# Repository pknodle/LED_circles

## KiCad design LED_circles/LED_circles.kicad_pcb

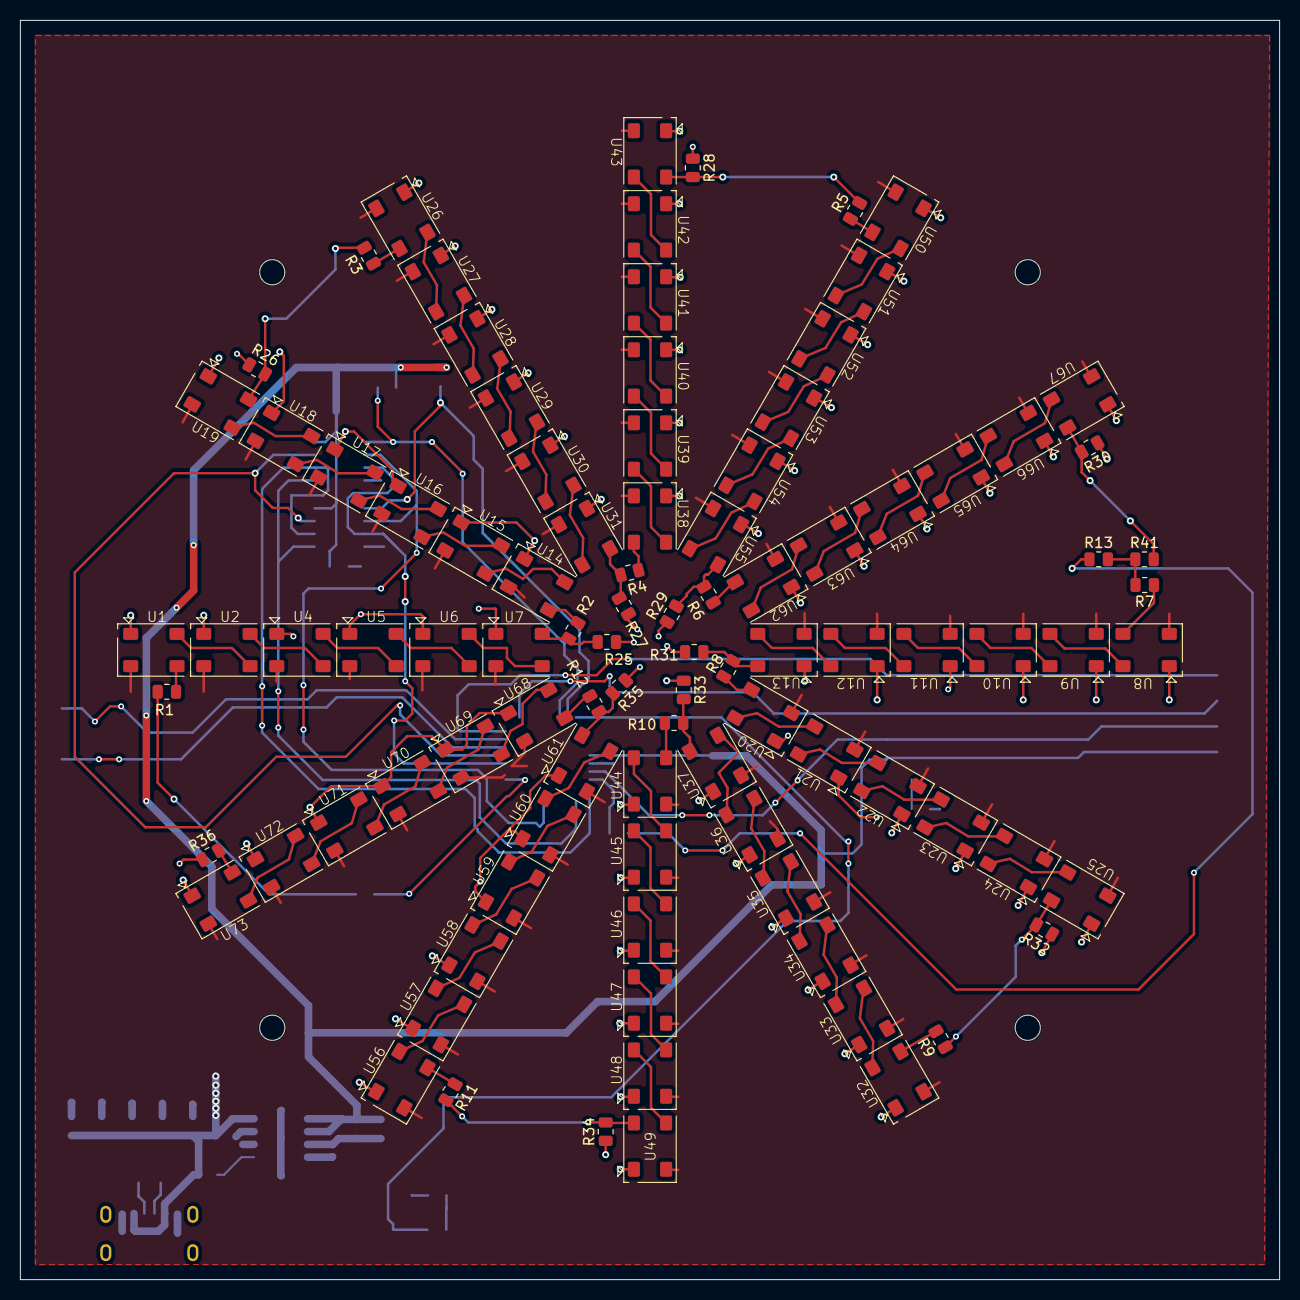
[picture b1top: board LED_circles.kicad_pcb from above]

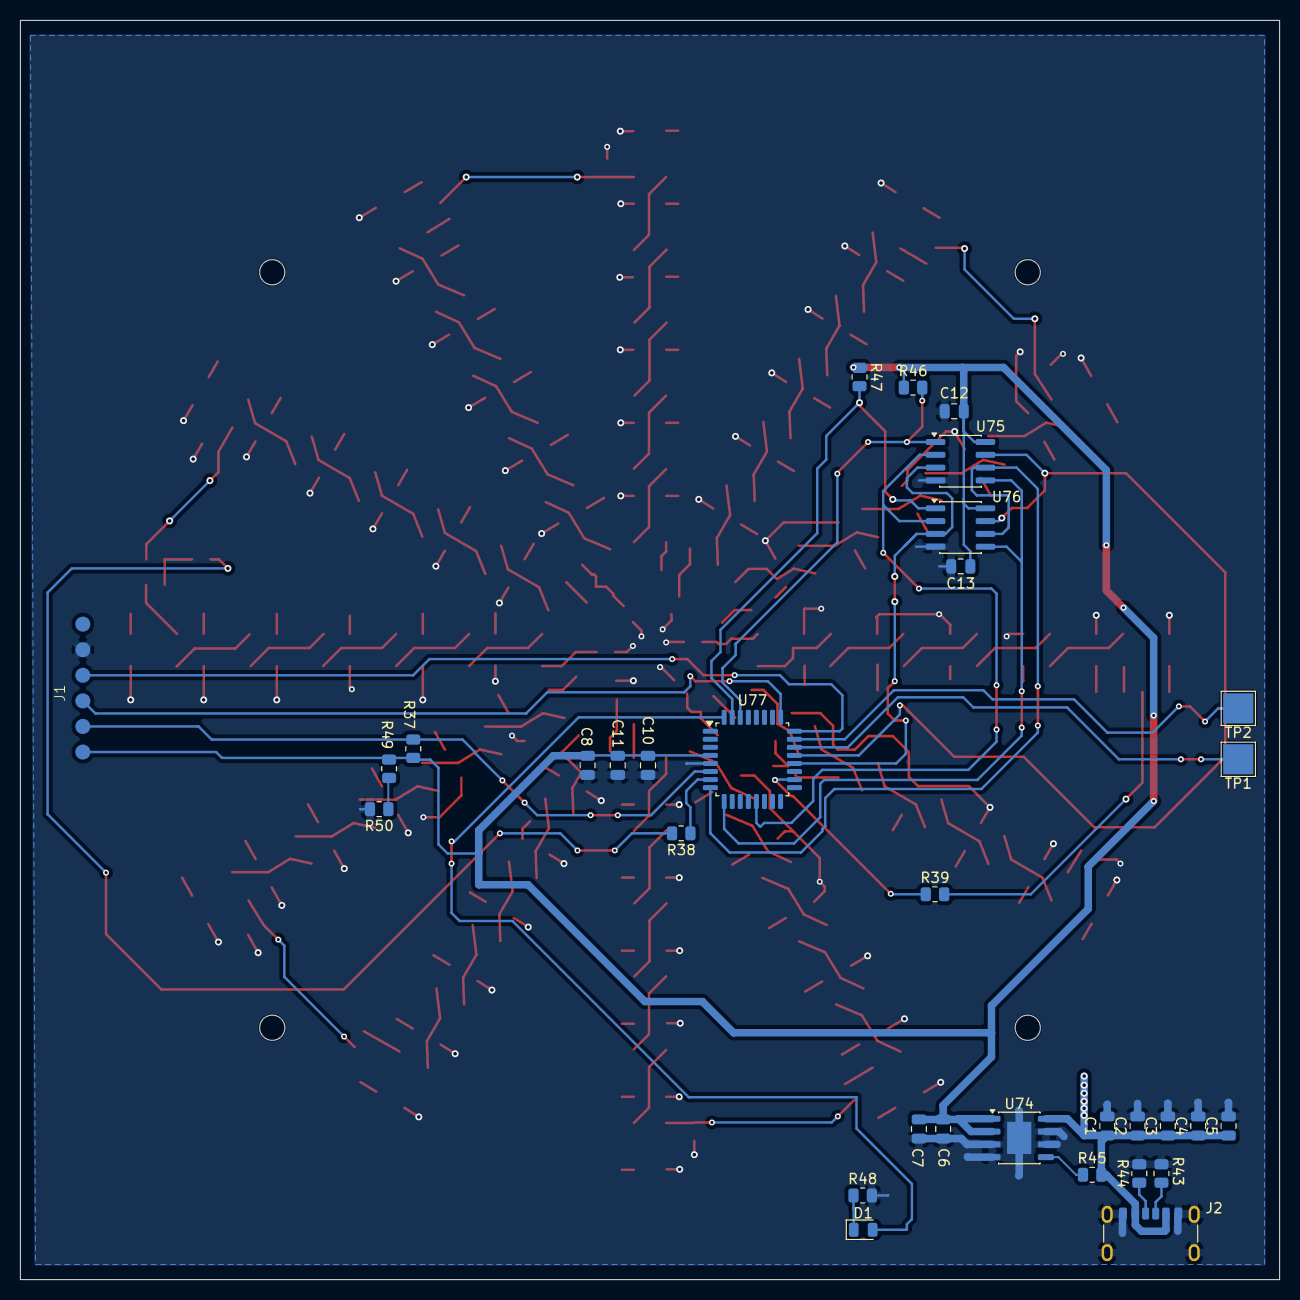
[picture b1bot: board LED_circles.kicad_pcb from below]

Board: 2 copper layers, 125.0 x 125.0 mm, 134 parts (32 on the bottom side), 110 nets.

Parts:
C1, C2, C3, C4, C5, C6, C7, C11: 10uF; C_0805_2012Metric
C8, C12, C13: .1uF; C_0805_2012Metric
C10: 1uF; C_0805_2012Metric
D1: LED; LED_0805_2012Metric
H1, H2, H3, H4: MountingHole; MountingHole_2.5mm
J1: Conn_ARM_SWD_EDGE; ARM_SWD_EDGE
J2: USB4125-GF-A; USB_C_Receptacle_GCT_USB4125-xx-x-0190_6P_TopMnt_Horizontal
R1, R2, R3, R4, R5, R6, R7, R8, R9, R10, R11, R12, R13, R25, R26, R27, R28, R29, R30, R31, R32, R33, R34, R35, R36, R41, R45: 0; R_0805_2012Metric
R37, R46, R47, R49, R50: 10k; R_0805_2012Metric
R38, R39: 500; R_0805_2012Metric
R43, R44: 5k1; R_0805_2012Metric
R48: 510; R_0805_2012Metric
TP1, TP2: TestPoint; TestPoint_Pad_3.0x3.0mm
U1, U2, U4, U5, U6, U7, U8, U9, U10, U11, U12, U13, U14, U15, U16, U17, U18, U19, U20, U21, U22, U23, U24, U25, U26, U27, U28, U29, U30, U31, U32, U33, U34, U35, U36, U37, U38, U39, U40, U41, U42, U43, U44, U45, U46, U47, U48, U49, U50, U51, U52, U53, U54, U55, U56, U57, U58, U59, U60, U61, U62, U63, U64, U65, U66, U67, U68, U69, U70, U71, U72, U73: IN-PI55TAT
U74: BD33GA3WEFJ; HTSOP-8-1EP_3.9x4.9mm_P1.27mm_EP2.4x3.2mm
U75, U76: M95256-WMN6P; SOIC-8_3.9x4.9mm_P1.27mm
U77: STM32G071KBTxN; LQFP-32_7x7mm_P0.8mm

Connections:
+3.3V: C6.1, C7.1, C8.1, C10.1, C11.1, C12.1, C13.1, J1.1 (VCC), R37.1, R46.1, R47.1, R49.1, U74.1 (VO), U74.2 (Vo_s), U75.8 (VCC), U76.8 (VCC), U77.4 (VDD)
+5V: C1.1, C2.1, C3.1, C4.1, C5.1, J2.A9 (VBUS_A9), J2.B9 (VBUS_B9), R45.2, U1.4 (VDD), U2.4 (VDD), U4.4 (VDD), U5.4 (VDD), U6.4 (VDD), U7.4 (VDD), U8.4 (VDD), U9.4 (VDD), U10.4 (VDD), U11.4 (VDD), U12.4 (VDD), U13.4 (VDD), U14.4 (VDD), U15.4 (VDD), U16.4 (VDD), U17.4 (VDD), U18.4 (VDD), U19.4 (VDD), U20.4 (VDD), U21.4 (VDD), U22.4 (VDD), U23.4 (VDD), U24.4 (VDD), U25.4 (VDD), U26.4 (VDD), U27.4 (VDD), U28.4 (VDD), U29.4 (VDD), U30.4 (VDD), U31.4 (VDD), U32.4 (VDD), U33.4 (VDD), U34.4 (VDD), U35.4 (VDD), U36.4 (VDD), U37.4 (VDD), U38.4 (VDD), U39.4 (VDD), U40.4 (VDD), U41.4 (VDD), U42.4 (VDD), U43.4 (VDD), U44.4 (VDD), U45.4 (VDD), U46.4 (VDD), U47.4 (VDD), U48.4 (VDD), U49.4 (VDD), U50.4 (VDD), U51.4 (VDD), U52.4 (VDD), U53.4 (VDD), U54.4 (VDD), U55.4 (VDD), U56.4 (VDD), U57.4 (VDD), U58.4 (VDD), U59.4 (VDD), U60.4 (VDD), U61.4 (VDD), U62.4 (VDD), U63.4 (VDD), U64.4 (VDD), U65.4 (VDD), U66.4 (VDD), U67.4 (VDD), U68.4 (VDD), U69.4 (VDD), U70.4 (VDD), U71.4 (VDD), U72.4 (VDD), U73.4 (VDD), U74.8 (VCC)
/LED_circles_ucontroller/BOOT0: R49.2, R50.1
/LED_circles_ucontroller/BOTTOM_ROWS: R13.1, R38.2
/LED_circles_ucontroller/EEPROM1_CS: R47.2, U76.1 (~S), U77.31 (PB7)
/LED_circles_ucontroller/EEPROM2_CS: R46.2, U75.1 (~S), U77.30 (PB6)
/LED_circles_ucontroller/HOLD: U75.7 (~HOLD), U76.7 (~HOLD), U77.21 (PA10/UCPD1_DBCC2)
/LED_circles_ucontroller/RX: TP2.1 (1_1), U77.23 (USART1_RX (PA10))
/LED_circles_ucontroller/SPI1_MISO: U75.2 (Q), U76.2 (Q), U77.13 (SPI1_MISO)
/LED_circles_ucontroller/SPI1_MOSI: U75.5 (D), U76.5 (D), U77.9 (SPI1_MOSI)
/LED_circles_ucontroller/SPI1_SCK: U75.6 (C), U76.6 (C), U77.8 (SPI1_SCK)
/LED_circles_ucontroller/SWCLK-BOOT0: J1.3 (SWCLK), U77.25 (SYS_SWCLK)
/LED_circles_ucontroller/SWDIO: J1.4 (SWDIO), U77.24 (SYS_SWDIO)
/LED_circles_ucontroller/TOP_ROWS: R1.1, R39.2
/LED_circles_ucontroller/TX: TP1.1 (1_1), U77.22 (USART1_TX (PA9))
/LED_circles_ucontroller/WRITE_PROTECT: U75.3 (~W), U76.3 (~W), U77.20 (PC6)
/Row1/DIN_{BOTTOM}: R7.1, R13.2, R41.1
/Row1/DOUT_{BOTTOM}: R8.1, R31.2, U13.2 (DOUT)
/Row1/DOUT_{TOP}: R2.1, R25.2, U7.2 (DOUT)
/Row2/DOUT_{BOTTOM}: R9.1, R32.2, U25.2 (DOUT)
/Row2/DOUT_{TOP}: R3.1, R26.2, U19.2 (DOUT)
/Row3/DOUT_{BOTTOM}: R10.1, R33.2, U37.2 (DOUT)
/Row3/DOUT_{TOP}: R4.1, R27.2, U31.2 (DOUT)
/Row4/DOUT_{BOTTOM}: R11.1, R34.2, U49.2 (DOUT)
/Row4/DOUT_{TOP}: R5.1, R28.2, U43.2 (DOUT)
/Row5/DOUT_{BOTTOM}: R12.1, R35.2, U61.2 (DOUT)
/Row5/DOUT_{TOP}: R6.1, R29.2, U55.2 (DOUT)
/Row6/DOUT_{BOTTOM}: R36.2, U73.2 (DOUT)
/Row6/DOUT_{TOP}: R30.2, R41.2, U67.2 (DOUT)
GND: C1.2, C2.2, C3.2, C4.2, C5.2, C6.2, C7.2, C8.2, C10.2, C11.2, C12.2, C13.2, J1.5 (GND), J2.A12 (GND_A12), J2.B12 (GND_B12), J2.SH (SHIELD_S1), R25.1, R26.1, R27.1, R28.1, R29.1, R30.1, R31.1, R32.1, R33.1, R34.1, R35.1, R36.1, R43.2, R44.2, R48.2, R50.2, U1.1 (GND), U2.1 (GND), U4.1 (GND), U5.1 (GND), U6.1 (GND), U7.1 (GND), U8.1 (GND), U9.1 (GND), U10.1 (GND), U11.1 (GND), U12.1 (GND), U13.1 (GND), U14.1 (GND), U15.1 (GND), U16.1 (GND), U17.1 (GND), U18.1 (GND), U19.1 (GND), U20.1 (GND), U21.1 (GND), U22.1 (GND), U23.1 (GND), U24.1 (GND), U25.1 (GND), U26.1 (GND), U27.1 (GND), U28.1 (GND), U29.1 (GND), U30.1 (GND), U31.1 (GND), U32.1 (GND), U33.1 (GND), U34.1 (GND), U35.1 (GND), U36.1 (GND), U37.1 (GND), U38.1 (GND), U39.1 (GND), U40.1 (GND), U41.1 (GND), U42.1 (GND), U43.1 (GND), U44.1 (GND), U45.1 (GND), U46.1 (GND), U47.1 (GND), U48.1 (GND), U49.1 (GND), U50.1 (GND), U51.1 (GND), U52.1 (GND), U53.1 (GND), U54.1 (GND), U55.1 (GND), U56.1 (GND), U57.1 (GND), U58.1 (GND), U59.1 (GND), U60.1 (GND), U61.1 (GND), U62.1 (GND), U63.1 (GND), U64.1 (GND), U65.1 (GND), U66.1 (GND), U67.1 (GND), U68.1 (GND), U69.1 (GND), U70.1 (GND), U71.1 (GND), U72.1 (GND), U73.1 (GND), U74.3 (GND), U74.4 (GND), U74.6 (GND), U74.7 (GND), U74.9 (GND), U75.4 (VSS), U76.4 (VSS), U77.5 (VSS)
unnamed: D1.2 (A), U77.32 (PB8)
unnamed: D1.1 (K), R48.1
unnamed: J1.2 (~RESET), R37.2, U77.6 (RCC_MCO)
unnamed: J2.A5 (CC1_A5), R44.1
unnamed: J2.B5 (CC2_B5), R43.1
unnamed: R1.2, U1.3 (DIN)
unnamed: U1.2 (DOUT), U2.3 (DIN)
unnamed: U2.2 (DOUT), U4.3 (DIN)
unnamed: U4.2 (DOUT), U5.3 (DIN)
unnamed: U5.2 (DOUT), U6.3 (DIN)
unnamed: U6.2 (DOUT), U7.3 (DIN)
unnamed: R7.2, U8.3 (DIN)
unnamed: U8.2 (DOUT), U9.3 (DIN)
unnamed: U9.2 (DOUT), U10.3 (DIN)
unnamed: U10.2 (DOUT), U11.3 (DIN)
unnamed: U11.2 (DOUT), U12.3 (DIN)
unnamed: U12.2 (DOUT), U13.3 (DIN)
unnamed: R2.2, U14.3 (DIN)
unnamed: U14.2 (DOUT), U15.3 (DIN)
unnamed: U15.2 (DOUT), U16.3 (DIN)
unnamed: U16.2 (DOUT), U17.3 (DIN)
unnamed: U17.2 (DOUT), U18.3 (DIN)
unnamed: U18.2 (DOUT), U19.3 (DIN)
unnamed: R8.2, U20.3 (DIN)
unnamed: U20.2 (DOUT), U21.3 (DIN)
unnamed: U21.2 (DOUT), U22.3 (DIN)
unnamed: U22.2 (DOUT), U23.3 (DIN)
unnamed: U23.2 (DOUT), U24.3 (DIN)
unnamed: U24.2 (DOUT), U25.3 (DIN)
unnamed: R3.2, U26.3 (DIN)
unnamed: U26.2 (DOUT), U27.3 (DIN)
unnamed: U27.2 (DOUT), U28.3 (DIN)
unnamed: U28.2 (DOUT), U29.3 (DIN)
unnamed: U29.2 (DOUT), U30.3 (DIN)
unnamed: U30.2 (DOUT), U31.3 (DIN)
unnamed: R9.2, U32.3 (DIN)
unnamed: U32.2 (DOUT), U33.3 (DIN)
unnamed: U33.2 (DOUT), U34.3 (DIN)
unnamed: U34.2 (DOUT), U35.3 (DIN)
unnamed: U35.2 (DOUT), U36.3 (DIN)
unnamed: U36.2 (DOUT), U37.3 (DIN)
unnamed: R4.2, U38.3 (DIN)
unnamed: U38.2 (DOUT), U39.3 (DIN)
unnamed: U39.2 (DOUT), U40.3 (DIN)
unnamed: U40.2 (DOUT), U41.3 (DIN)
unnamed: U41.2 (DOUT), U42.3 (DIN)
unnamed: U42.2 (DOUT), U43.3 (DIN)
unnamed: R10.2, U44.3 (DIN)
unnamed: U44.2 (DOUT), U45.3 (DIN)
unnamed: U45.2 (DOUT), U46.3 (DIN)
unnamed: U46.2 (DOUT), U47.3 (DIN)
unnamed: U47.2 (DOUT), U48.3 (DIN)
unnamed: U48.2 (DOUT), U49.3 (DIN)
unnamed: R5.2, U50.3 (DIN)
unnamed: U50.2 (DOUT), U51.3 (DIN)
unnamed: U51.2 (DOUT), U52.3 (DIN)
unnamed: U52.2 (DOUT), U53.3 (DIN)
unnamed: U53.2 (DOUT), U54.3 (DIN)
unnamed: U54.2 (DOUT), U55.3 (DIN)
unnamed: R11.2, U56.3 (DIN)
unnamed: U56.2 (DOUT), U57.3 (DIN)
unnamed: U57.2 (DOUT), U58.3 (DIN)
unnamed: U58.2 (DOUT), U59.3 (DIN)
unnamed: U59.2 (DOUT), U60.3 (DIN)
unnamed: U60.2 (DOUT), U61.3 (DIN)
unnamed: R6.2, U62.3 (DIN)
unnamed: U62.2 (DOUT), U63.3 (DIN)
unnamed: U63.2 (DOUT), U64.3 (DIN)
unnamed: U64.2 (DOUT), U65.3 (DIN)
unnamed: U65.2 (DOUT), U66.3 (DIN)
unnamed: U66.2 (DOUT), U67.3 (DIN)
unnamed: R12.2, U68.3 (DIN)
unnamed: U68.2 (DOUT), U69.3 (DIN)
unnamed: U69.2 (DOUT), U70.3 (DIN)
unnamed: U70.2 (DOUT), U71.3 (DIN)
unnamed: U71.2 (DOUT), U72.3 (DIN)
unnamed: U72.2 (DOUT), U73.3 (DIN)
unnamed: R45.1, U74.5 (EN)
unnamed: R38.1, U77.7 (TIM2_CH1)
unnamed: R39.1, U77.18 (TIM1_CH1)

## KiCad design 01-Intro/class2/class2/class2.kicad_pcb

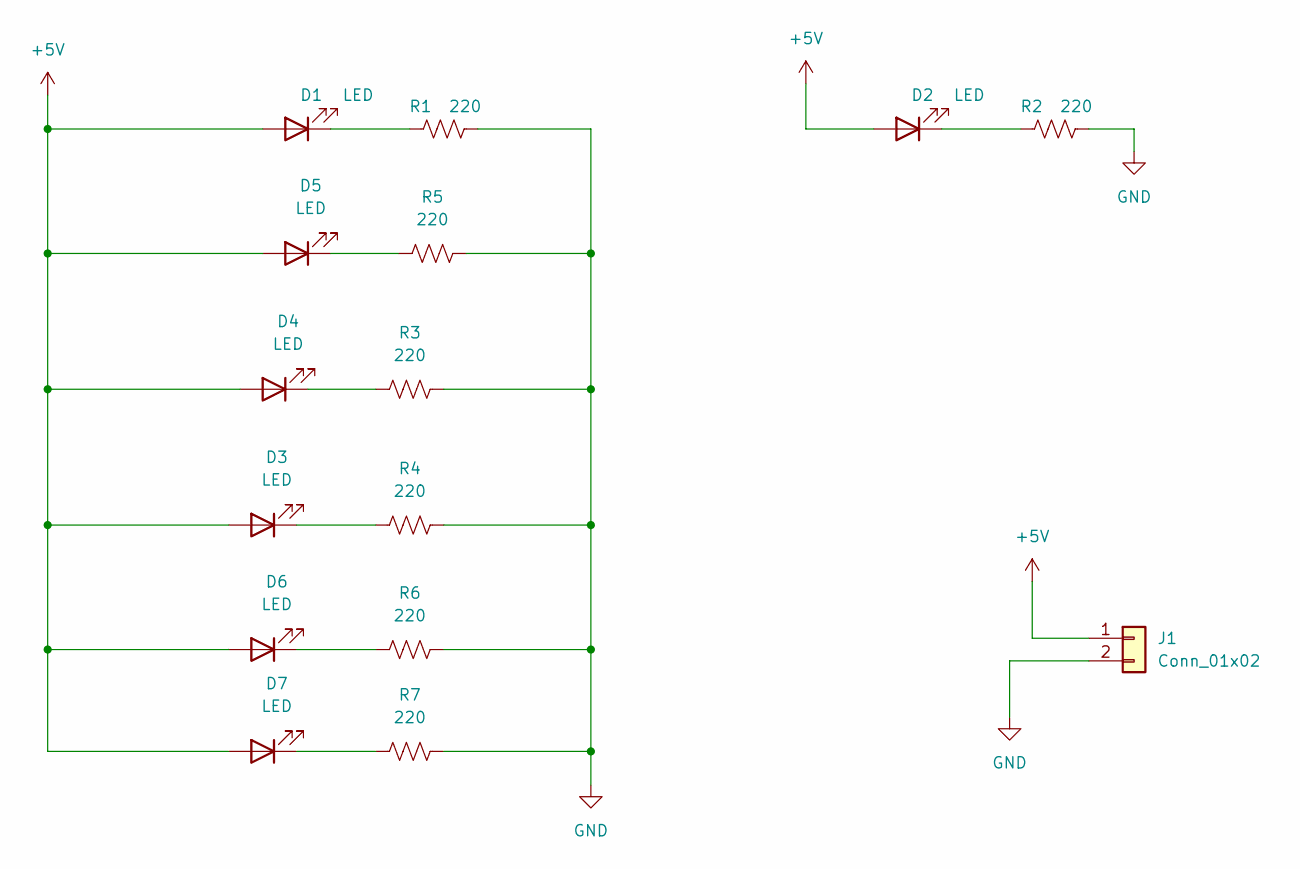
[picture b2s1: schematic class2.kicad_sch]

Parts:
D1, D2, D3, D4, D5, D6, D7: LED; LED_D5.0mm
J1: Conn_01x02; PinHeader_1x02_P2.54mm_Horizontal
R1, R2, R3, R4, R5, R6, R7: 220; R_0805_2012Metric_Pad1.20x1.40mm_HandSolder

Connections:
+5V: D1.2 (A), D2.2 (A), D3.2 (A), D4.2 (A), D5.2 (A), D6.2 (A), D7.2 (A), J1.1
GND: J1.2, R1.2, R2.2, R3.2, R4.2, R5.2, R6.2, R7.2
unnamed: D1.1 (K), R1.1
unnamed: D2.1 (K), R2.1
unnamed: D3.1 (K), R4.1
unnamed: D4.1 (K), R3.1
unnamed: D5.1 (K), R5.1
unnamed: D6.1 (K), R6.1
unnamed: D7.1 (K), R7.1

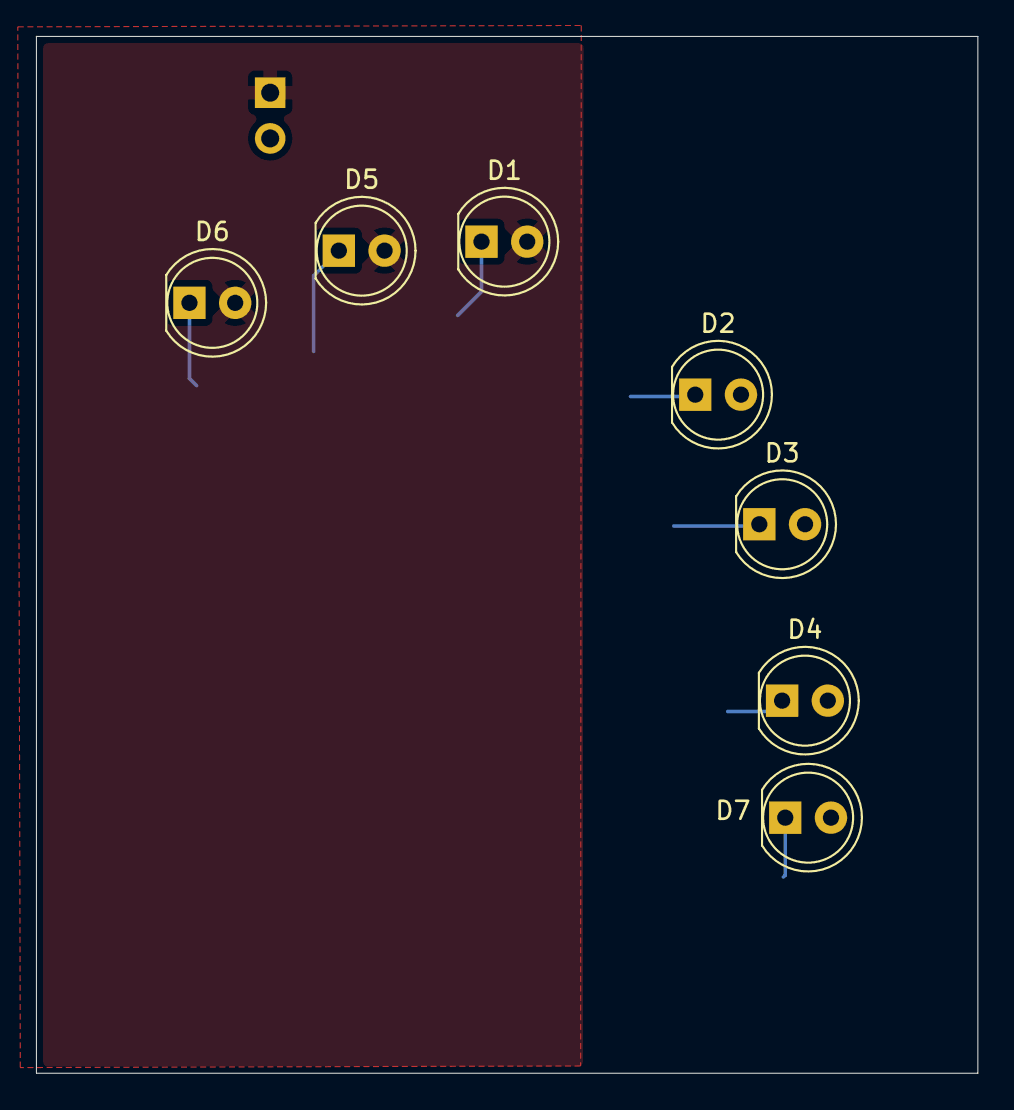
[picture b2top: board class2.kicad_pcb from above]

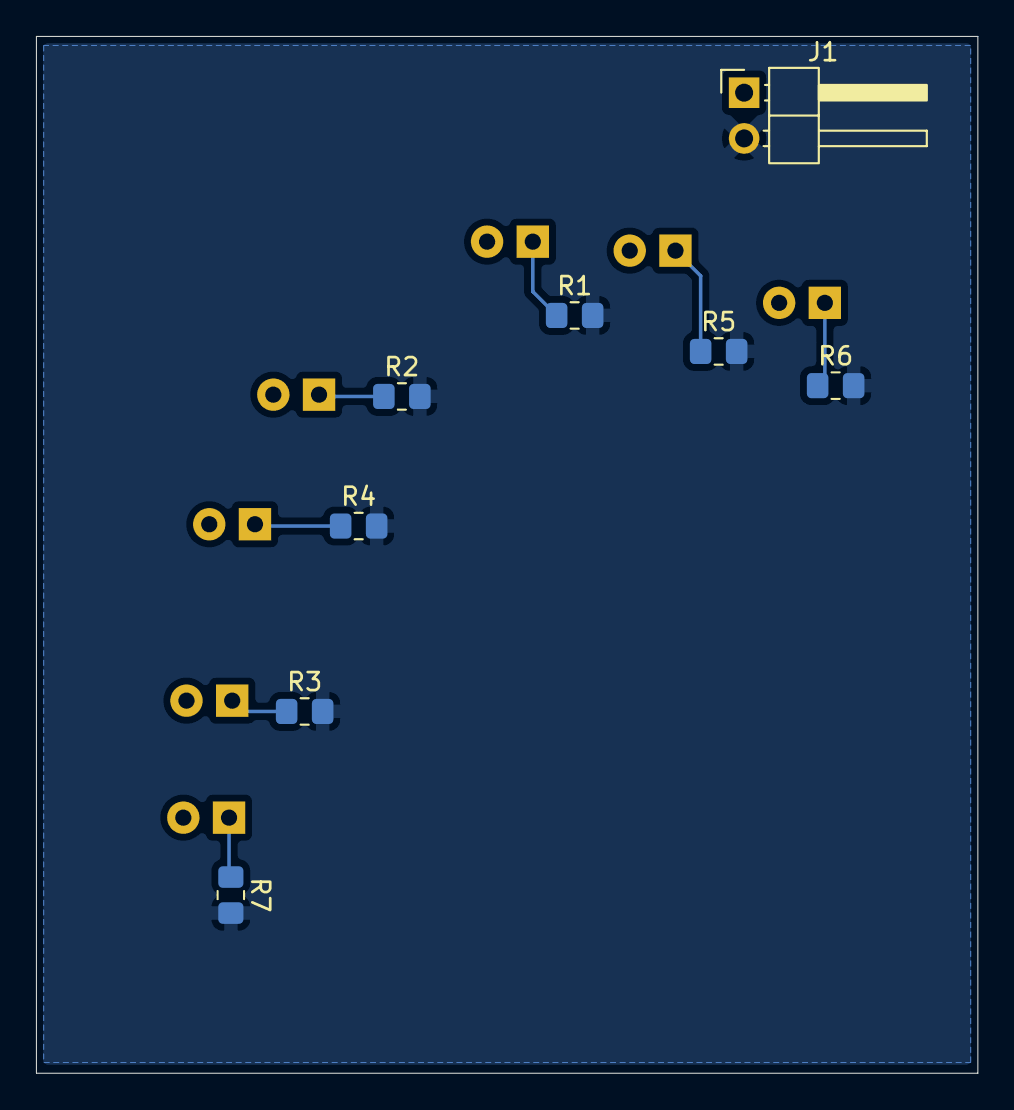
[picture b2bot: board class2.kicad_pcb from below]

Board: 2 copper layers, 52.3 x 57.6 mm, 15 parts (8 on the bottom side), 9 nets.

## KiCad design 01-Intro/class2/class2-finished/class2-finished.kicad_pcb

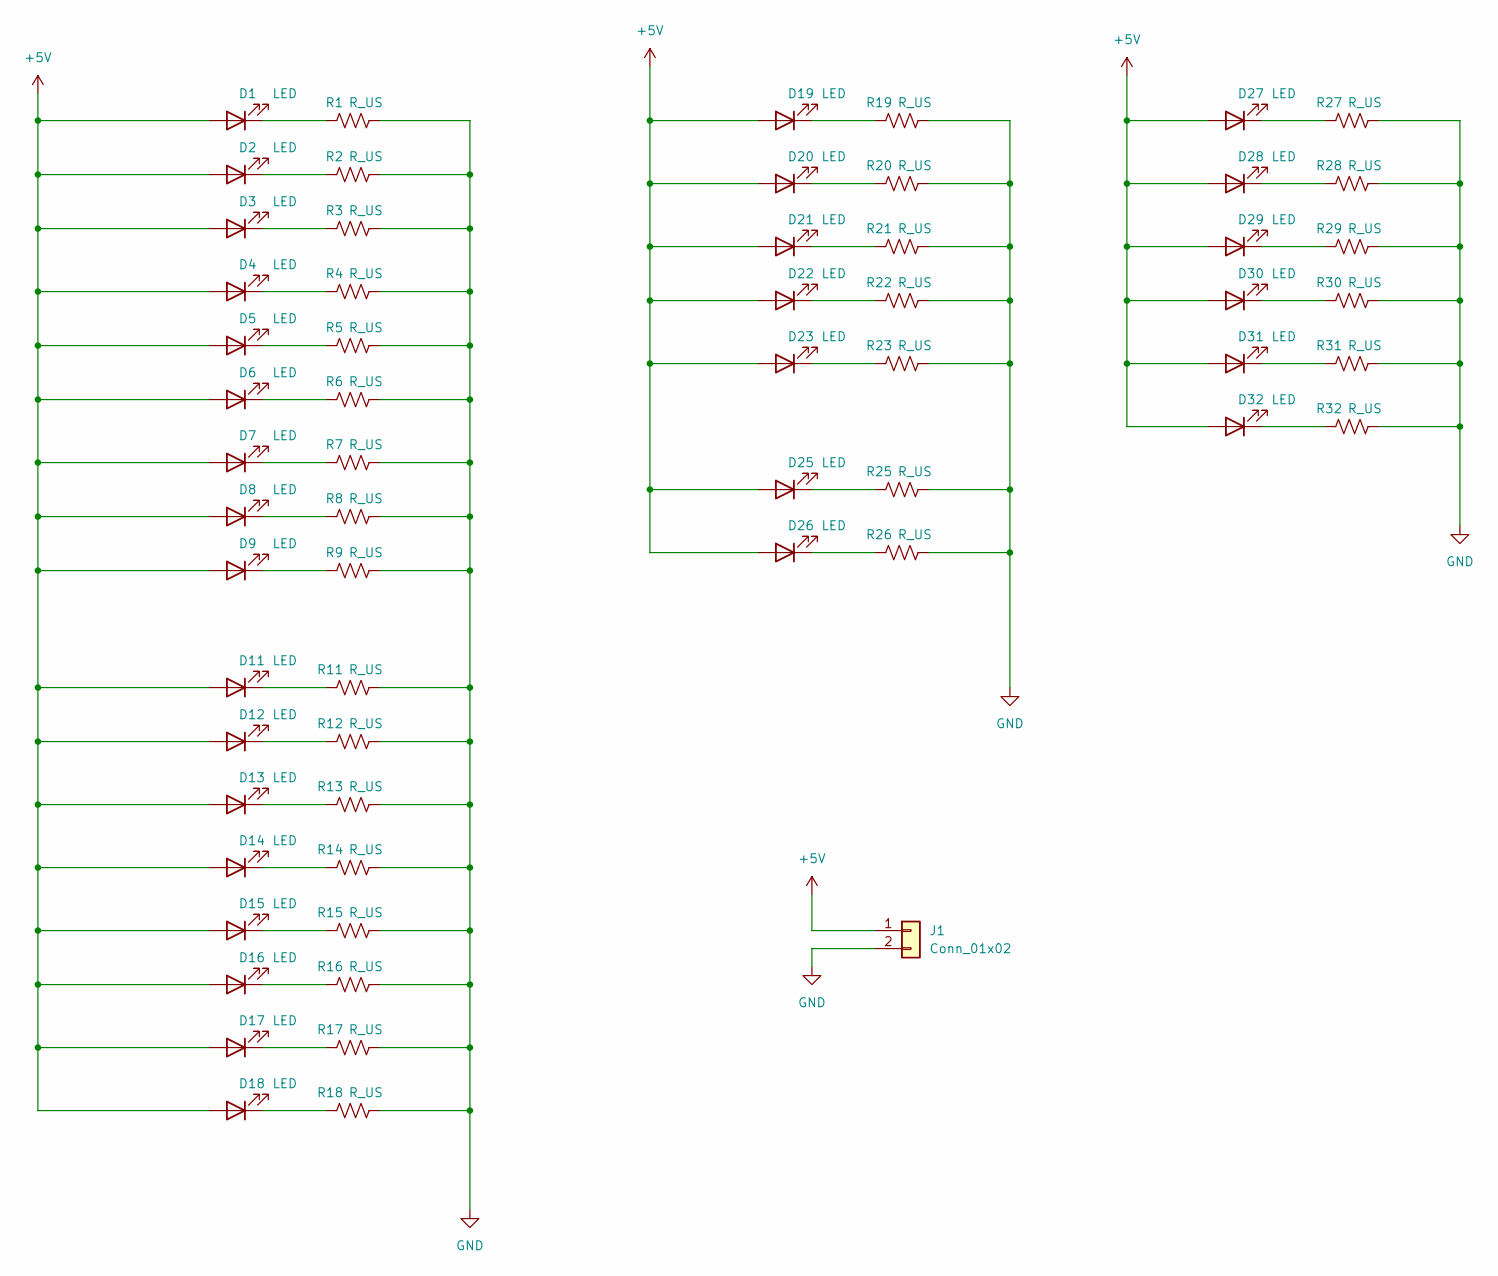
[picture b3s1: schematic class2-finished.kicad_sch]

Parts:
D1, D2, D3, D4, D5, D6, D7, D8, D9, D11, D12, D13, D14, D15, D16, D17, D18, D19, D20, D21, D22, D23, D25, D26, D27, D28, D29, D30, D31, D32: LED; LED_D5.0mm
J1: Conn_01x02; PhoenixContact_SPT_1.5_2-H-3.5_1x02_P3.5mm_Horizontal
R1, R2, R3, R4, R5, R6, R7, R8, R9, R11, R12, R13, R14, R15, R16, R17, R18, R19, R20, R21, R22, R23, R25, R26, R27, R28, R29, R30, R31, R32: R_US; R_0805_2012Metric

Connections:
+5V: D1.2 (A), D2.2 (A), D3.2 (A), D4.2 (A), D5.2 (A), D6.2 (A), D7.2 (A), D8.2 (A), D9.2 (A), D11.2 (A), D12.2 (A), D13.2 (A), D14.2 (A), D15.2 (A), D16.2 (A), D17.2 (A), D18.2 (A), D19.2 (A), D20.2 (A), D21.2 (A), D22.2 (A), D23.2 (A), D25.2 (A), D26.2 (A), D27.2 (A), D28.2 (A), D29.2 (A), D30.2 (A), D31.2 (A), D32.2 (A), J1.1
GND: J1.2, R1.2, R2.2, R3.2, R4.2, R5.2, R6.2, R7.2, R8.2, R9.2, R11.2, R12.2, R13.2, R14.2, R15.2, R16.2, R17.2, R18.2, R19.2, R20.2, R21.2, R22.2, R23.2, R25.2, R26.2, R27.2, R28.2, R29.2, R30.2, R31.2, R32.2
unnamed: D1.1 (K), R1.1
unnamed: D2.1 (K), R2.1
unnamed: D3.1 (K), R3.1
unnamed: D4.1 (K), R4.1
unnamed: D5.1 (K), R5.1
unnamed: D6.1 (K), R6.1
unnamed: D7.1 (K), R7.1
unnamed: D8.1 (K), R8.1
unnamed: D9.1 (K), R9.1
unnamed: D11.1 (K), R11.1
unnamed: D12.1 (K), R12.1
unnamed: D13.1 (K), R13.1
unnamed: D14.1 (K), R14.1
unnamed: D15.1 (K), R15.1
unnamed: D16.1 (K), R16.1
unnamed: D17.1 (K), R17.1
unnamed: D18.1 (K), R18.1
unnamed: D19.1 (K), R19.1
unnamed: D20.1 (K), R20.1
unnamed: D21.1 (K), R21.1
unnamed: D22.1 (K), R22.1
unnamed: D23.1 (K), R23.1
unnamed: D25.1 (K), R25.1
unnamed: D26.1 (K), R26.1
unnamed: D27.1 (K), R27.1
unnamed: D28.1 (K), R28.1
unnamed: D29.1 (K), R29.1
unnamed: D30.1 (K), R30.1
unnamed: D31.1 (K), R31.1
unnamed: D32.1 (K), R32.1

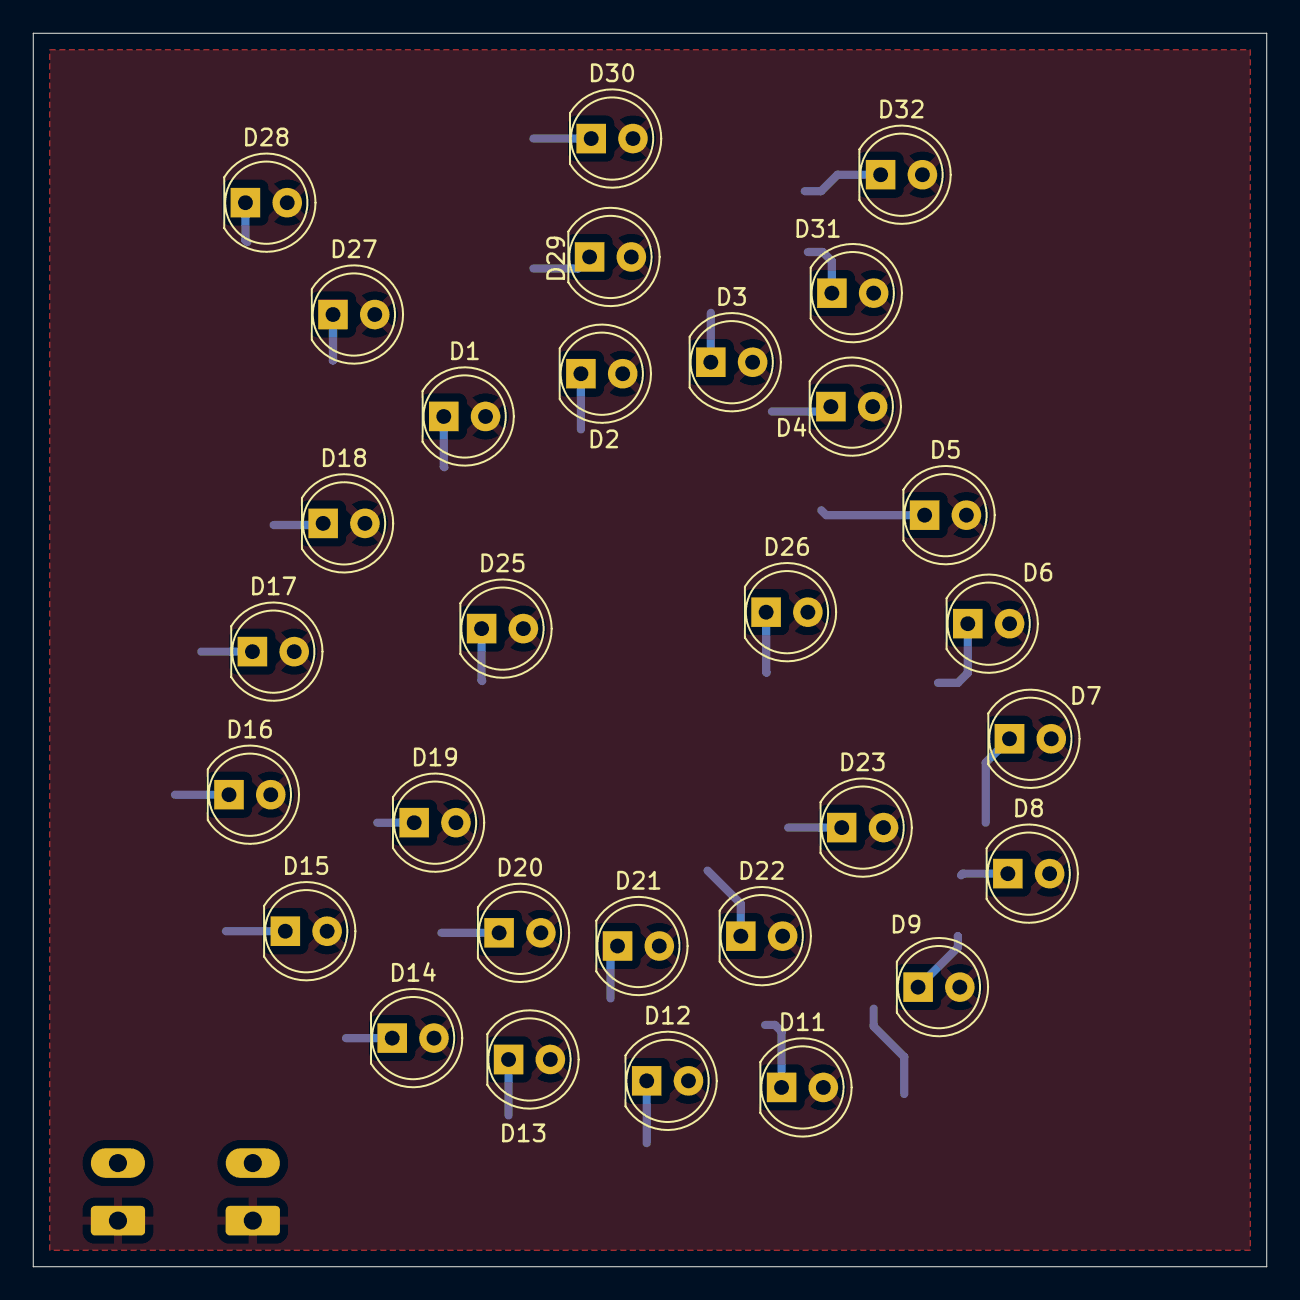
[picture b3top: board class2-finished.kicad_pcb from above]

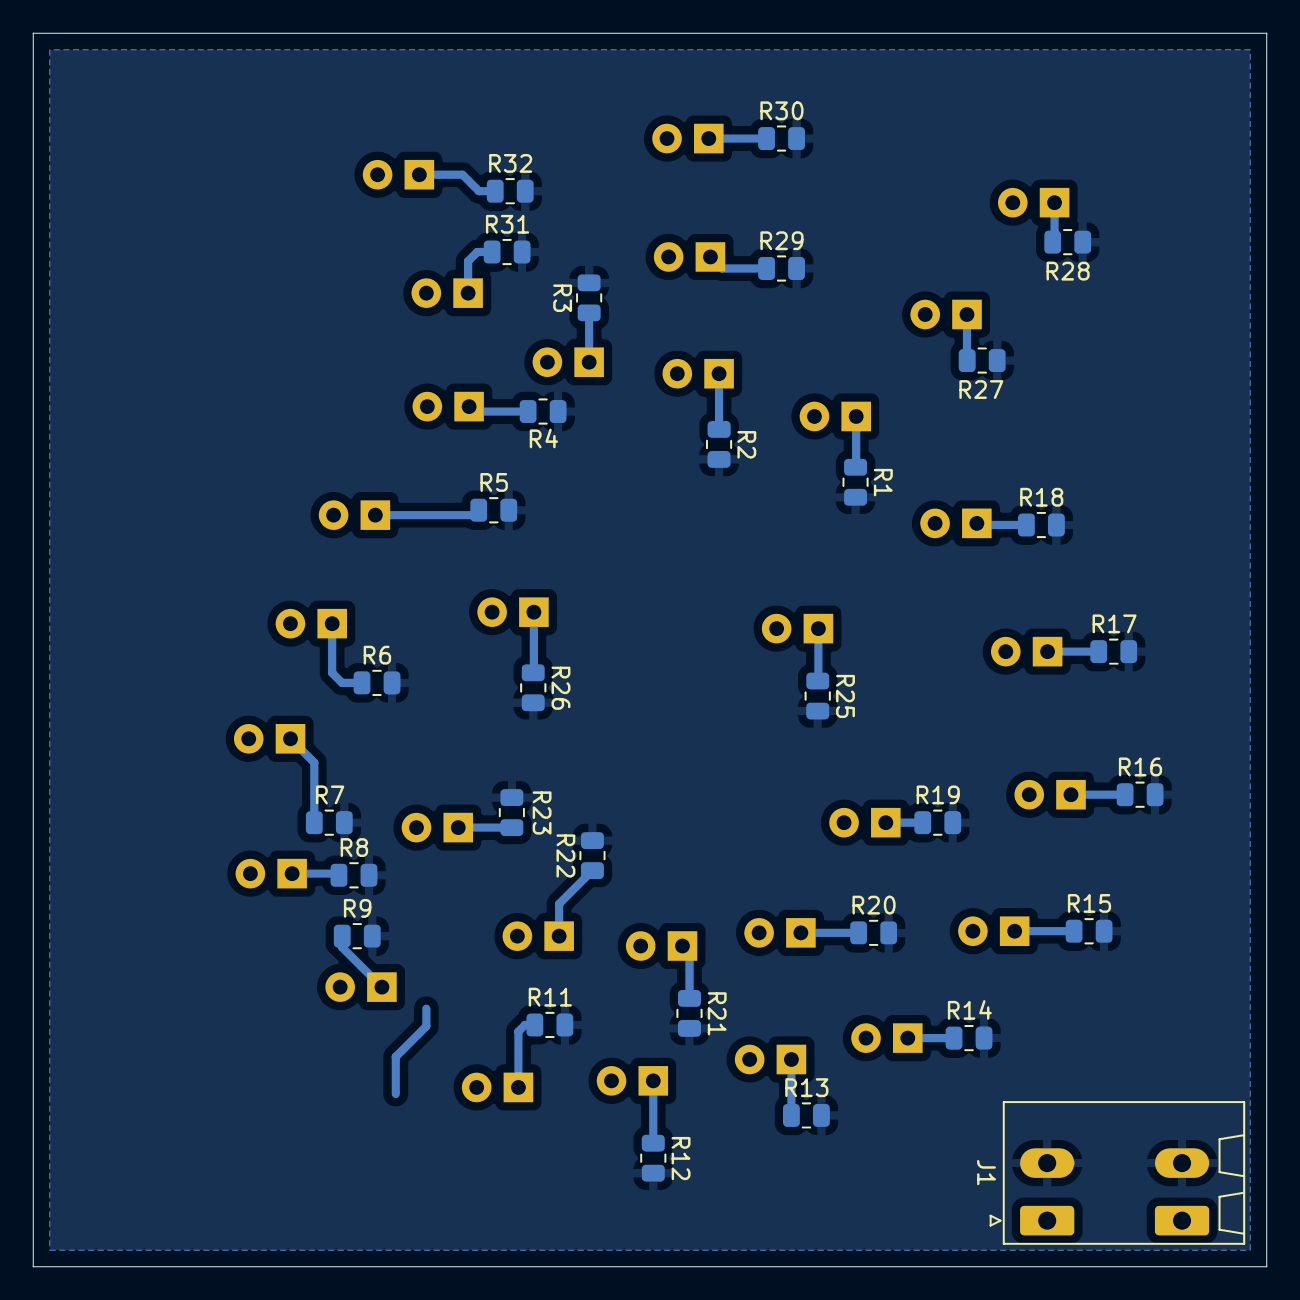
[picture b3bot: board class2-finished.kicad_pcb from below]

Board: 2 copper layers, 75.0 x 75.0 mm, 61 parts (31 on the bottom side), 32 nets.

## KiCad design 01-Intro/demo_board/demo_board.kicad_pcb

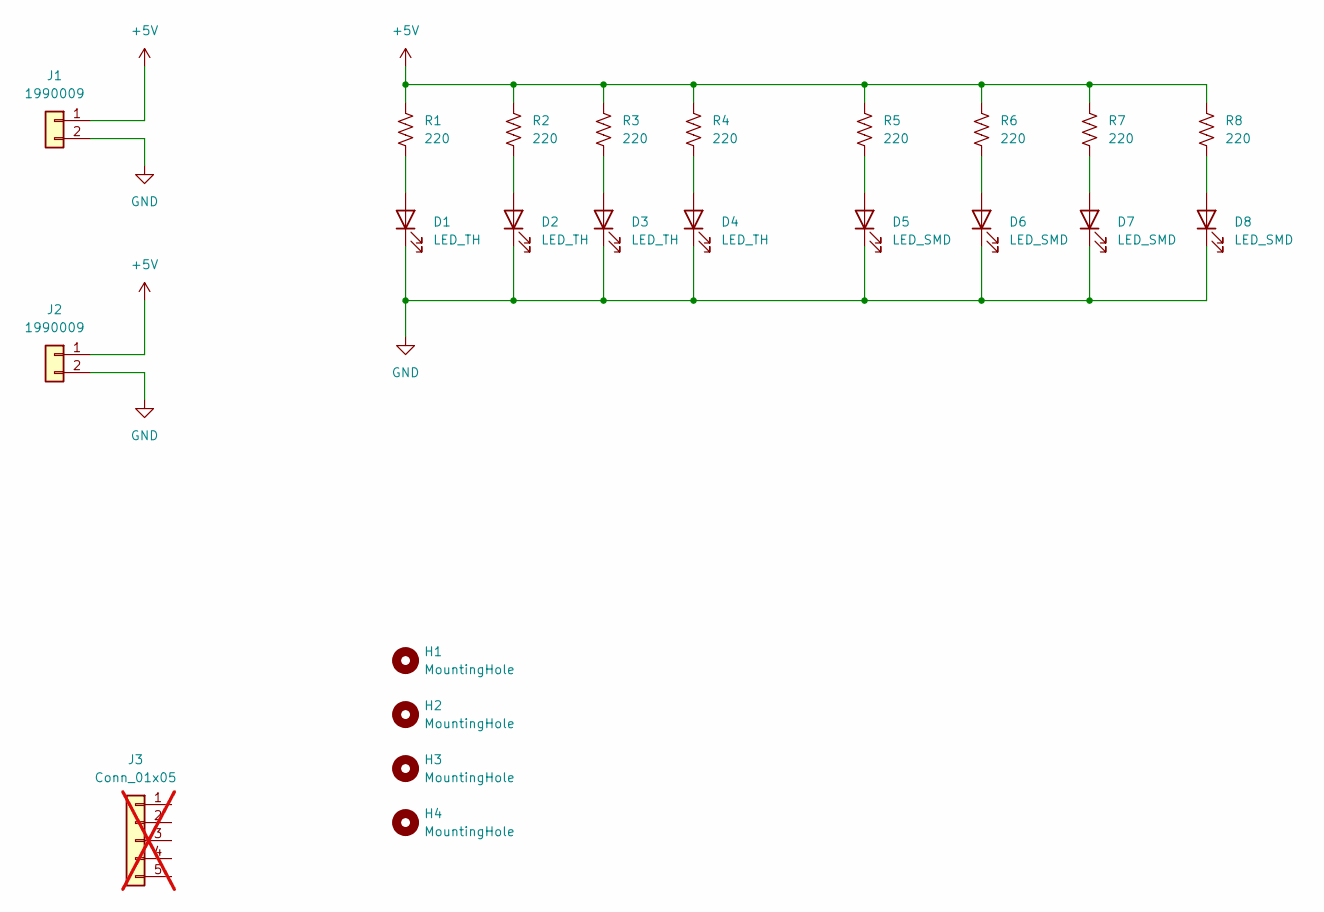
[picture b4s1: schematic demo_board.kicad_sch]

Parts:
D1, D2, D3, D4: LED_TH; LED_D5.0mm
D5, D6, D7, D8: LED_SMD; LED_0805_2012Metric_Pad1.15x1.40mm_HandSolder
H1, H2, H3, H4: MountingHole; MountingHole_3.5mm
J1, J2: 1990009; Phoenix_1990009
J3: Conn_01x05; PinHeader_1x05_P2.00mm_Vertical; not fitted
R1, R2, R3, R4, R5, R6, R7, R8: 220; R_0805_2012Metric_Pad1.20x1.40mm_HandSolder

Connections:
+5V: J1.1, J2.1, R1.1, R2.1, R3.1, R4.1, R5.1, R6.1, R7.1, R8.1
GND: D1.1 (K), D2.1 (K), D3.1 (K), D4.1 (K), D5.1 (K), D6.1 (K), D7.1 (K), D8.1 (K), J1.2, J2.2
unnamed: D1.2 (A), R1.2
unnamed: D2.2 (A), R2.2
unnamed: D3.2 (A), R3.2
unnamed: D4.2 (A), R4.2
unnamed: D5.2 (A), R5.2
unnamed: D6.2 (A), R6.2
unnamed: D7.2 (A), R7.2
unnamed: D8.2 (A), R8.2

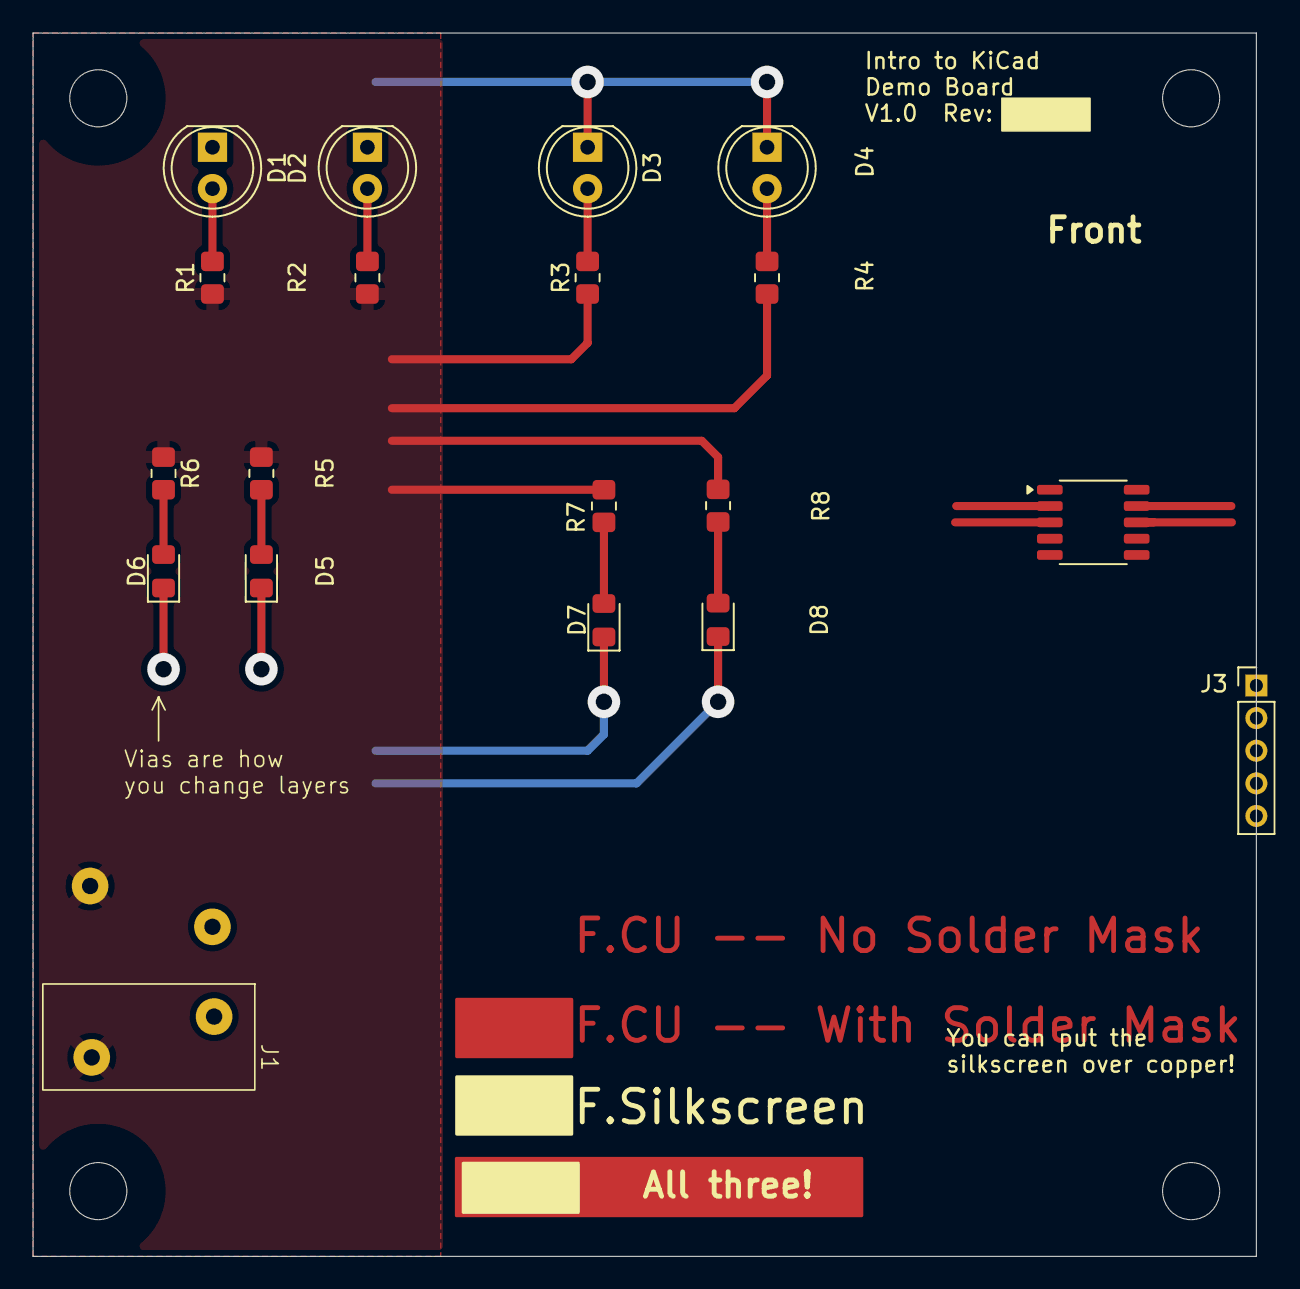
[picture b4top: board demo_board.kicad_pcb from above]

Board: 2 copper layers, 75.0 x 75.0 mm, 23 parts (1 on the bottom side), 10 nets.

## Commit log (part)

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2025-06-09 Initial desing
2025-06-09 Added LED placement script
2025-06-09 Initial Schematic and LED Placement
2025-07-12 Initial layout of top layer
2025-07-13 Inital layout
2025-07-13 Added all connections to PCB
2025-07-13 Fixed PCB DRC issues.
2025-07-13 Removed unnecessary jumper resistor
2025-09-06 Tweaks
2025-09-14 Changed micro controller to larger package
    - Also changed PCB DRC to work with OSH Park
    - Changed SWD connection to generic 0.1" pogopin headers
2025-10-05 reverted back to power only USB
2025-11-30 More layout
2025-12-02 Pin swapping on pogo pins
2025-12-02 Fixed connectivity problems
2025-12-02 Fixed DRC issues
2025-12-02 Fixed silkscreen issues
2025-12-06 Updated pcb to fix pcb/schematic parity DRC error
2025-12-06 Deleted parts not used in single row test PCB
2025-12-06 Shrunk board outline to 94mm x 75mm
2025-12-06 Made vias really big so one can make them on a circuit mill
2025-12-07 Changed plane thermal relief to use normal traces
    This aids in manufacturability on a PCB mill. You only need to mill out one trace instead of thermal spokes.
2025-12-20 Increased track width
2026-04-07 Moved LED_circles
2026-04-14 Added demo board
